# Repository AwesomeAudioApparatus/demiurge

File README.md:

# Demiurge

Demiurge is a combination of Hardware and Software for Digital Sound Processing in the Eurorack Modular Synthesizer environment.

The "Demiurge 1" board is an 8 HP Eurorack compatible board, the functionality defined in software and custom front panel can either 
be made by hand, ordered from local mechanical shops or ordered from PCB manufacturers (KiCad template for front panel exists).

The "Demiurge Sound Processing Engine" is a system to more easily create Eurorack module functionality. A simple VCO module may look like this;

```C
#include "demiurge.h"
#include "demiurge-board.h"

static control_pair_t pair1;  // frequency
static control_pair_t pair2;  // amplitude

static control_pair_t pair3;  // frequency
static control_pair_t pair4;  // amplitude

static audio_outport_t out1;
static audio_outport_t out2;
static oscillator_t oscillator1;
static oscillator_t oscillator2;

/* Simple 2 VCO. SAW on output 1 and SQUARE on output 2. */

void vco_prepare() {
    demiurge_samplerate = 48000;      // 48000 samples/second
    demiurge_set_inport_cv(1);
    demiurge_set_inport_cv(2);
    demiurge_set_inport_cv(3);
    demiurge_set_inport_cv(4);

    demiurge_set_outport_audio(1);
    demiurge_set_outport_audio(2);
}

void vco_setup() {
    // Initialize the hardware configuration
    control_pair_init(&pair1, 1);     // FREQUENCY = CV+Pot at the top
    control_pair_init(&pair2, 2);     // AMPLITUDE = CV+Pot at the second position from the top
    control_pair_init(&pair3, 3);     // FREQUENCY = CV+Pot at the third position from top
    control_pair_init(&pair4, 4);     // AMPLITUDE = CV+Pot at the bottom
    audio_outport_init(&out1, 1);     // Audio Out on left output channel
    audio_outport_init(&out2, 2);     // Audio Out on right output channel

    // Initialize the oscillators
    oscillator_init(&oscillator1);
    oscillator_init(&oscillator2);

    // Set up the oscillators to SINE wave form

    oscillator_configure_mode(&oscillator1, SAW);
    oscillator_configure_mode(&oscillator2, SQUARE);

    oscillator_configure_frequency(&oscillator1, &pair1.me);
    oscillator_configure_frequency(&oscillator2, &pair3.me);

    oscillator_configure_amplitude(&oscillator1, &pair2.me);
    oscillator_configure_amplitude(&oscillator2, &pair4.me);

    // Connect Oscillator to outputs
    audio_outport_configure_input(&out1, &oscillator1.me);
    audio_outport_configure_input(&out2, &oscillator2.me);
}

void vco_loop() {
   // handle buttons and LEDs
}

int main(void)
{
    vco_prepare();                  // Prepare the board for the functionality

    demiurge_driver_init();         // Initialize the hardware driver
    demiurge_init();                // Initialize the Demiurge platform
    vco_setup();                    // Set up the functionality
    demiurge_start();               // Start the audio processing
    while(1)
    {
        vco_loop();                 // Give time for LEDs and Buttons
    }
}

```

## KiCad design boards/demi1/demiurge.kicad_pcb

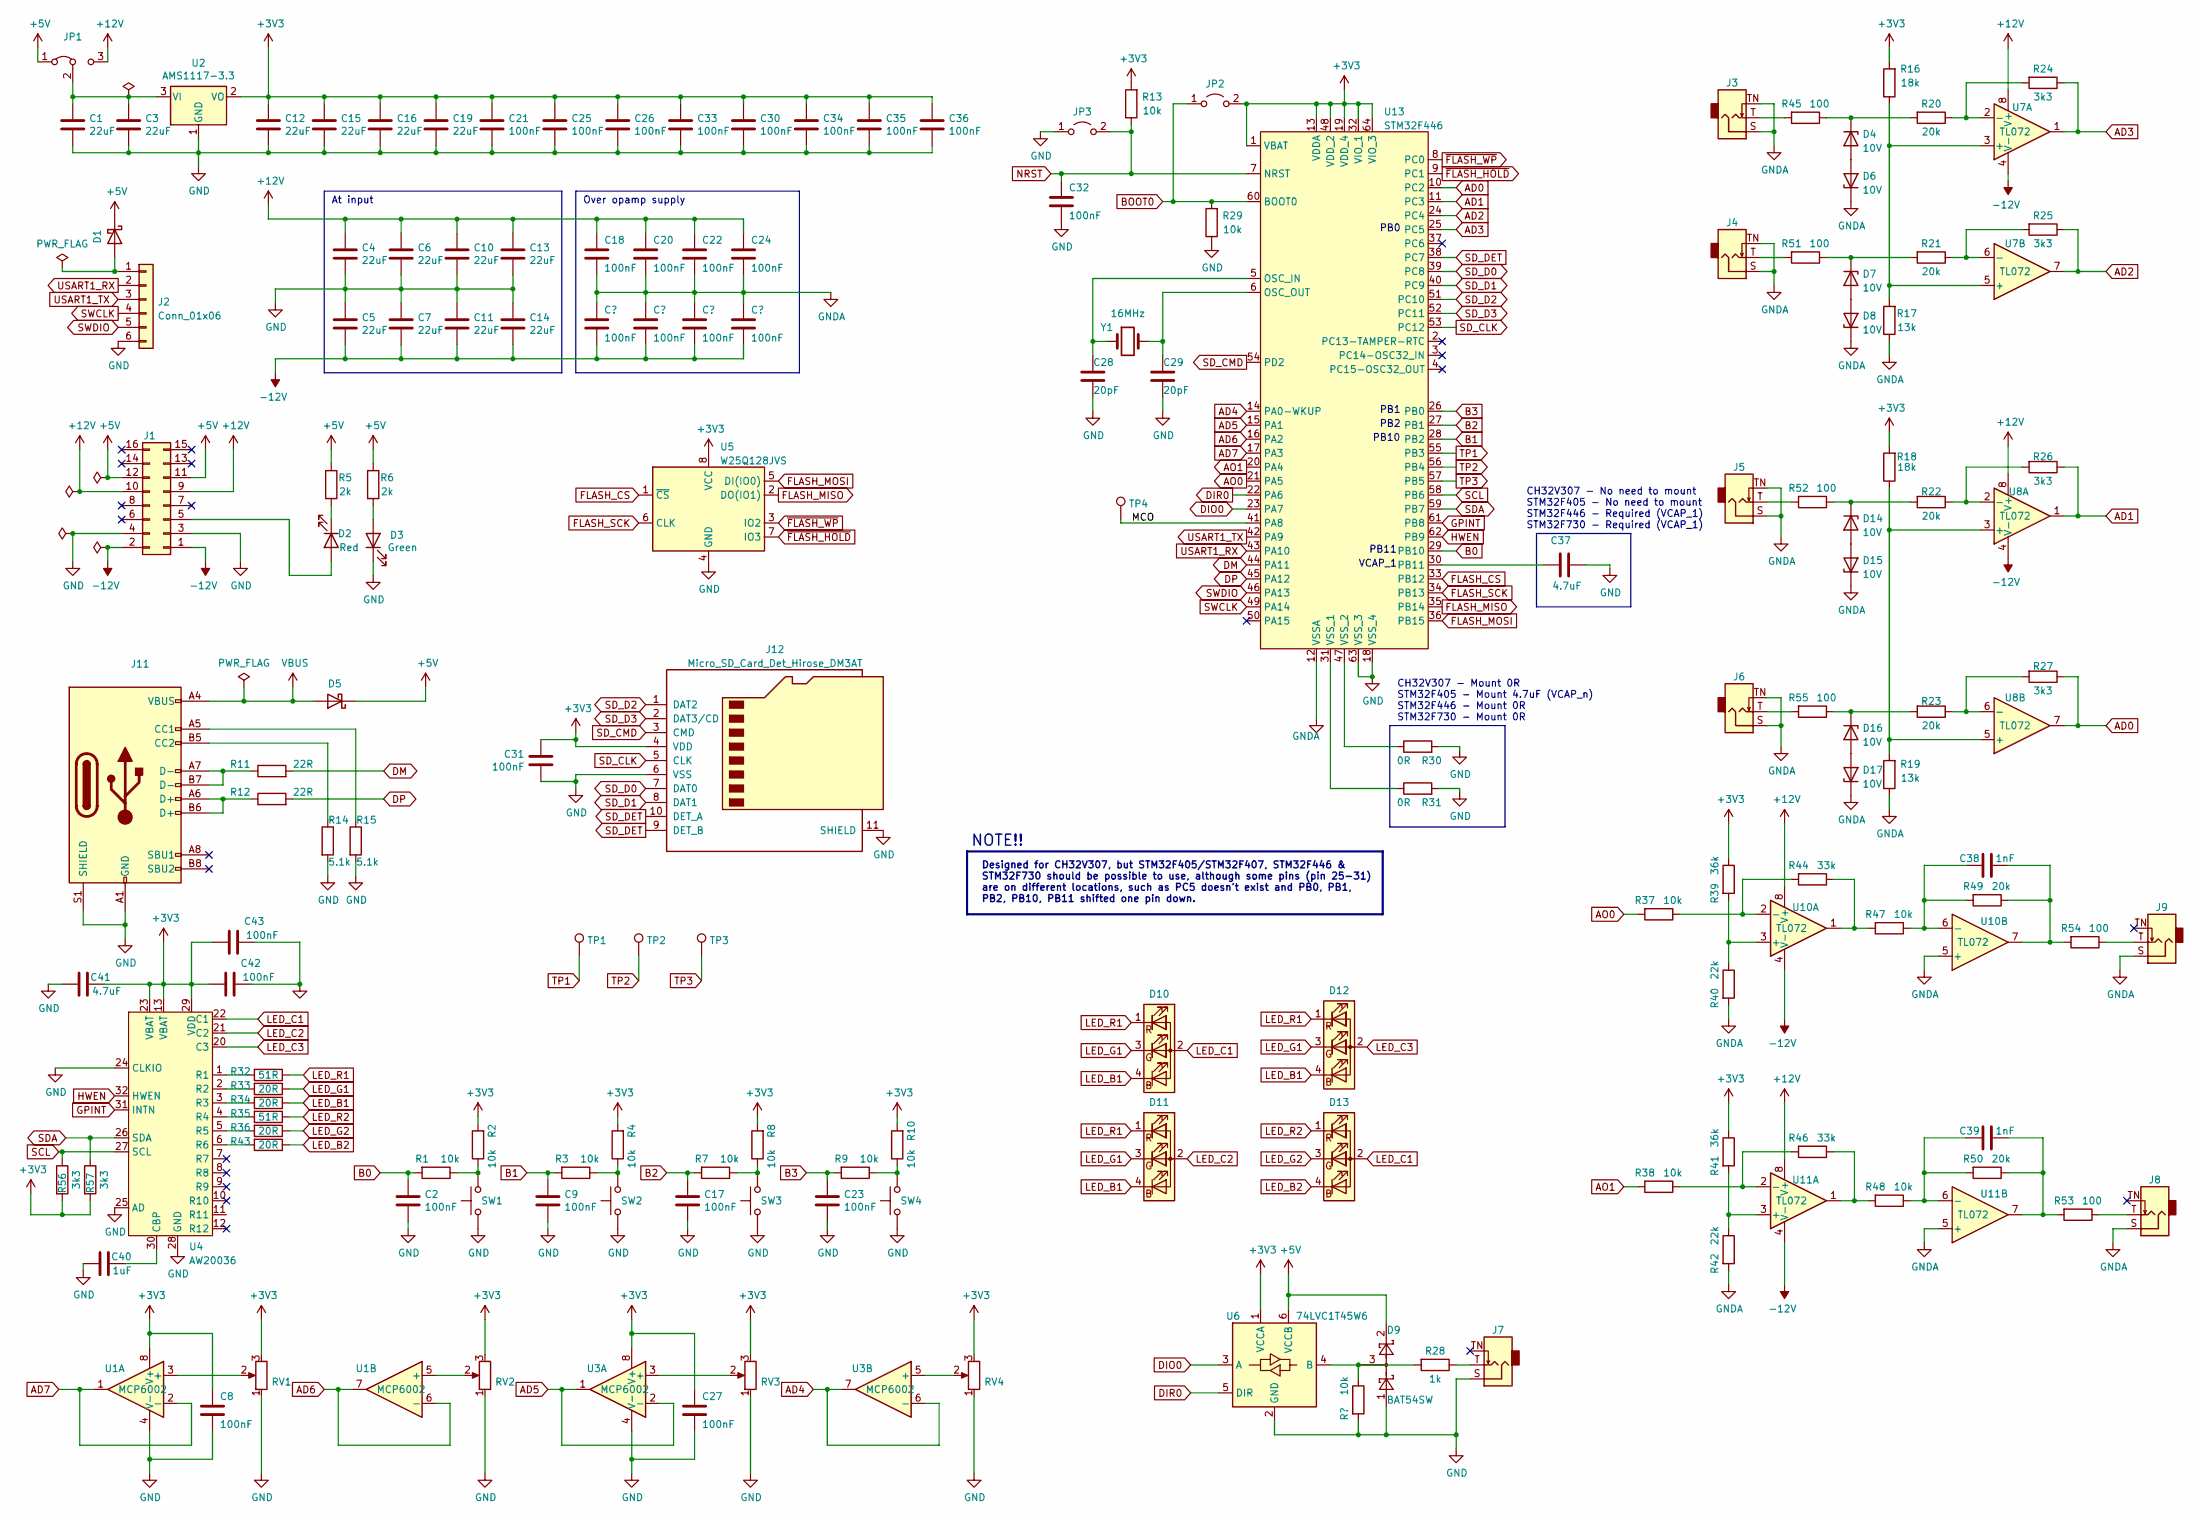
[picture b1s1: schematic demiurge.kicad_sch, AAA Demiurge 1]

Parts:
C1, C3, C4, C5, C6, C7, C10, C11, C12, C13, C14, C15, C16, C19: 22uF; C_0805_2012Metric; LCSC C129303
C2, C8, C9, C17, C18, C20, C21, C22, C23, C24, C25, C26, C27, C30, C31, C32, C33, C34, C35, C36, C42, C43: 100nF; C_0603_1608Metric; LCSC C14663
C28, C29: 20pF; C_0603_1608Metric; LCSC C1648
C37, C41: 4.7uF; C_0805_2012Metric; LCSC C19666
C38, C39: 1nF; C_0603_1608Metric; LCSC C1588
C40: 1uF; C_0603_1608Metric; LCSC C15849
D1, D5: D_SOD-123; LCSC C8598
D2: Red; LED_0603_1608Metric; LCSC C2286
D3: Green; LED_0603_1608Metric; LCSC C72043
D4, D6, D7, D8, D14, D15, D16, D17: 10V; D_SOD-323; LCSC C493185
D9: BAT54SW; SOT-323_SC-70; LCSC C78260
D10, D11, D12, D13: LED_D5.0mm-4_RGB; LCSC C331057
J1: PinHeader_2x08_P2.54mm_Vertical; LCSC C68234
J2: Conn_01x06; PinHeader_1x06_P2.54mm_Vertical; LCSC C37208
J3, J4, J5, J6, J7, J8, J9: PJ301M-12
J11: USB_C_Receptacle_Vertical; LCSC C167321
J12: Micro_SD_Card_Det_Hirose_DM3AT; microSD_HC_Hirose_DM3AT-SF-PEJM5; LCSC C114218
JP1: SolderJumper-3_P1.3mm_Bridged12_RoundedPad1.0x1.5mm
JP2, JP3: C_1206_3216Metric
R1, R2, R3, R4, R7, R8, R9, R10, R13, R29, R37, R38, R47, R48: 10k; R_0603_1608Metric; LCSC C25804
R5, R6: 2k; R_0603_1608Metric; LCSC C22975
R11, R12: 22R; R_0402_1005Metric; LCSC C25092
R14, R15: 5.1k; R_0402_1005Metric; LCSC C25905
R16, R18: 18k; R_0603_1608Metric; LCSC C25810
R17, R19: 13k; R_0603_1608Metric; LCSC C22797
R20, R21, R22, R23, R49, R50: 20k; R_0603_1608Metric; LCSC C4184
R24, R25, R26, R27, R56, R57: 3k3; R_0603_1608Metric; LCSC C22978
R28: 1k; R_0603_1608Metric; LCSC C21190
R30, R31: 0R; C_0603_1608Metric; LCSC C21189
R32, R35: 51R; R_0603_1608Metric; LCSC C23197
R33, R34, R36, R43: 20R; R_0603_1608Metric; LCSC C22950
R39, R41: 36k; R_0603_1608Metric; LCSC C23147
R40, R42: 22k; R_0603_1608Metric; LCSC C31850
R44, R46: 33k; R_0603_1608Metric; LCSC C4216
R45, R51, R52, R53, R54, R55: 100; R_0603_1608Metric; LCSC C22775
RV1, RV2, RV3, RV4: Potentiometer_Alpha_RD901F-40-00D_Single_Vertical
SW1, SW2, SW3, SW4: SW_PUSH_6mm_H8mm
TP1: TP1; TestPoint_Pad_1.5x1.5mm
TP2: TP2; TestPoint_Pad_1.5x1.5mm
TP3, TP4: SWO; TestPoint_Pad_1.5x1.5mm
U1, U3: MCP6002; SOIC-8_3.9x4.9mm_P1.27mm; LCSC C7377
U2: AMS1117-3.3; SOT-223-3_TabPin2; LCSC C6186
U4: AW20036; QFN-32-1EP_4x4mm_P0.4mm_EP2.65x2.65mm_ThermalVias; LCSC C401019
U5: W25Q128JVS; SOIC-8_5.23x5.23mm_P1.27mm; LCSC C97521
U6: 74LVC1T45W6; SOT-23-6; LCSC C7843
U7, U8, U10, U11: TL072; SOIC-8_3.9x4.9mm_P1.27mm; LCSC C6961
U13: STM32F446; LQFP-64_10x10mm_P0.5mm; LCSC C69336
Y1: 16MHz; Crystal_SMD_3225-4Pin_3.2x2.5mm; LCSC C13738

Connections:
+3V3: C8.1, C12.1, C15.1, C16.1, C19.1, C21.1, C25.1, C26.1, C27.1, C30.1, C31.1, C33.1, C34.1, C35.1, C36.1, C41.2, C42.1, C43.1, J12.4 (VDD), JP2.2 (B), R2.2, R4.2, R8.2, R10.2, R13.2, R16.2, R18.2, R39.1, R41.1, R56.2, R57.2, RV1.3, RV2.3, RV3.3, RV4.3, U1.8 (V+), U2.2 (VO), U3.8 (V+), U4.13 (VBAT), U4.23 (VBAT), U4.29 (VDD), U5.8 (VCC), U6.1 (VCCA), U13.1 (VBAT), U13.13 (VDDA), U13.19 (VDD_4), U13.32 (VIO_1), U13.48 (VDD_2), U13.64 (VIO_3)
+5V: D1.1 (K), D5.1 (K), D9.2, J1.11, J1.12, JP1.1 (A), R5.1, R6.1, U6.6 (VCCB)
+12V: C4.1, C6.1, C10.1, C13.1, C18.1, C20.1, C22.1, C24.1, J1.9, J1.10, JP1.3 (B), U7.8 (V+), U8.8 (V+), U10.8 (V+), U11.8 (V+)
/MCO: TP4.1, U13.41 (PA8)
AD0: R27.1, U8.7, U13.10 (PC2)
AD1: R26.1, U8.1, U13.11 (PC3)
AD2: R25.1, U7.7, U13.24 (PC4)
AD3: R24.1, U7.1, U13.25 (PC5)
AD4: U3.6 (-), U3.7, U13.14 (PA0-WKUP)
AD5: U3.1, U3.2 (-), U13.15 (PA1)
AD6: U1.6 (-), U1.7, U13.16 (PA2)
AD7: U1.1, U1.2 (-), U13.17 (PA3)
AO0: R37.2, U13.21 (PA5)
AO1: R38.2, U13.20 (PA4)
B0: C2.1, R1.2, U13.29 (PB10)
B1: C9.1, R3.2, U13.28 (PB2)
B2: C17.1, R7.2, U13.27 (PB1)
B3: C23.1, R9.2, U13.26 (PB0)
BOOT0: JP2.1 (A), R29.2, U13.60 (BOOT0)
DIO0: U6.3 (A), U13.23 (PA7)
DIR0: U6.5 (DIR), U13.22 (PA6)
DM: R11.2, U13.44 (PA11)
DP: R12.2, U13.45 (PA12)
FLASH_CS: U5.1 (~CS), U13.33 (PB12)
FLASH_MISO: U5.2 (DO(IO1)), U13.35 (PB14)
FLASH_MOSI: U5.5 (DI(IO0)), U13.36 (PB15)
FLASH_SCK: U5.6 (CLK), U13.34 (PB13)
GND: C1.2, C2.2, C3.2, C4.2, C5.1, C6.2, C7.1, C8.2, C9.2, C10.2, C11.1, C12.2, C13.2, C14.1, C15.2, C16.2, C17.2, C19.2, C21.2, C23.2, C25.2, C26.2, C27.2, C28.2, C29.2, C30.2, C31.2, C32.2, C33.2, C34.2, C35.2, C36.2, C37.2, C40.1, C41.1, C42.2, C43.2, D3.1 (K), D9.1, J1.3, J1.4, J2.6, J7.S, J11.A1 (GND), J11.A12 (GND), J11.B1 (GND), J11.B12 (GND), J11.S1 (SHIELD), J12.6 (VSS), J12.11 (SHIELD), JP3.1 (A), R14.2, R15.2, R29.1, R30.2, R31.2, RV1.1, RV2.1, RV3.1, RV4.1, SW1.1, SW2.1, SW3.1, SW4.1, U1.4 (V-), U2.1 (GND), U3.4 (V-), U4.24 (CLKIO), U4.25 (AD), U4.28 (GND), U5.4 (GND), U6.2 (GND), U13.18 (VSS_4), U13.63 (VSS_3)
GNDA: D6.1 (K), D8.1 (K), D15.1 (K), D17.1 (K), J3.S, J3.TN, J4.S, J4.TN, J5.S, J5.TN, J6.S, J6.TN, J8.S, J9.S, R17.1, R19.1, R40.2, R42.2, U10.5 (+), U11.5 (+), U13.12 (VSSA)
GPINT: U4.31 (INTN), U13.61 (PB8)
HWEN: U4.32 (HWEN), U13.62 (PB9)
LED_B1: D10.4 (BK), D11.4 (BK), D12.4 (BK), R34.1
LED_B2: D13.4 (BK), R43.1
LED_C1: D10.2 (A), D13.2 (A), U4.22 (C1)
LED_C2: D11.2 (A), U4.21 (C2)
LED_C3: D12.2 (A), U4.20 (C3)
LED_G1: D10.3 (GK), D11.3 (GK), D12.3 (GK), R33.1
LED_G2: D13.3 (GK), R36.1
LED_R1: D10.1 (RK), D11.1 (RK), D12.1 (RK), R32.1
LED_R2: D13.1 (RK), R35.1
NRST: C32.1, JP3.2 (B), R13.1, U13.7 (NRST)
unnamed: C1.1, C3.1, JP1.2 (C), U2.3 (VI)
unnamed: C28.1, U13.5 (OSC_IN), Y1.1
unnamed: C29.1, U13.6 (OSC_OUT), Y1.2
unnamed: C37.1, U13.30 (PB11)
unnamed: C38.1, R47.1, R49.2, U10.6 (-)
unnamed: C38.2, R49.1, R54.2, U10.7
unnamed: C39.1, R48.1, R50.2, U11.6 (-)
unnamed: C39.2, R50.1, R53.2, U11.7
unnamed: C40.2, U4.30 (CBP)
unnamed: D1.2 (A), J2.1
unnamed: D2.1 (K), R5.2
unnamed: D2.2 (A), J1.5
unnamed: D3.2 (A), R6.2
unnamed: D4.1 (K), R20.2, R45.1
unnamed: D4.2 (A), D6.2 (A)
unnamed: D7.1 (K), R21.2, R51.1
unnamed: D7.2 (A), D8.2 (A)
unnamed: D9.3, R28.2, U6.4 (B)
unnamed: D14.1 (K), R22.2, R52.1
unnamed: D14.2 (A), D15.2 (A)
unnamed: D16.1 (K), R23.2, R55.1
unnamed: D16.2 (A), D17.2 (A)
unnamed: J3.T, R45.2
unnamed: J4.T, R51.2
unnamed: J5.T, R52.2
unnamed: J6.T, R55.2
unnamed: J7.T, R28.1
unnamed: J8.T, R53.1
unnamed: J9.T, R54.1
unnamed: J11.A5 (CC1), R15.1
unnamed: J11.A6 (D+), J11.B6 (D+), R12.1
unnamed: J11.A7 (D-), J11.B7 (D-), R11.1
unnamed: J11.B5 (CC2), R14.1
unnamed: R1.1, R2.1, SW1.2
unnamed: R3.1, R4.1, SW2.2
unnamed: R7.1, R8.1, SW3.2
unnamed: R9.1, R10.1, SW4.2
unnamed: R16.1, R17.2, U7.3 (+), U7.5 (+)
unnamed: R18.1, R19.2, U8.3 (+), U8.5 (+)
unnamed: R20.1, R24.2, U7.2 (-)
unnamed: R21.1, R25.2, U7.6 (-)
unnamed: R22.1, R26.2, U8.2 (-)
unnamed: R23.1, R27.2, U8.6 (-)
unnamed: R30.1, U13.47 (VSS_2)
unnamed: R31.1, U13.31 (VSS_1)
unnamed: R32.2, U4.1 (R1)
unnamed: R33.2, U4.2 (R2)
unnamed: R34.2, U4.3 (R3)
unnamed: R35.2, U4.4 (R4)
unnamed: R36.2, U4.5 (R5)
unnamed: R37.1, R44.2, U10.2 (-)
unnamed: R38.1, R46.2, U11.2 (-)
unnamed: R39.2, R40.1, U10.3 (+)
unnamed: R41.2, R42.1, U11.3 (+)
unnamed: R43.2, U4.6 (R6)
unnamed: R44.1, R47.2, U10.1
unnamed: R46.1, R48.2, U11.1
unnamed: RV1.2, U1.3 (+)
unnamed: RV2.2, U1.5 (+)
unnamed: RV3.2, U3.3 (+)
unnamed: RV4.2, U3.5 (+)
SCL: R56.1, U4.27 (SCL), U13.58 (PB6)
SDA: R57.1, U4.26 (SDA), U13.59 (PB7)
SD_CLK: J12.5 (CLK), U13.53 (PC12)
SD_CMD: J12.3 (CMD), U13.54 (PD2)
SD_D0: J12.7 (DAT0), U13.39 (PC8)
SD_D1: J12.8 (DAT1), U13.40 (PC9)
SD_D2: J12.1 (DAT2), U13.51 (PC10)
SD_D3: J12.2 (DAT3/CD), U13.52 (PC11)
SD_DET: J12.9 (DET_B), J12.10 (DET_A), U13.38 (PC7)
SWCLK: J2.4, U13.49 (PA14)
SWDIO: J2.5, U13.46 (PA13)
TP1: TP1.1, U13.55 (PB3)
TP2: TP2.1, U13.56 (PB4)
TP3: TP3.1, U13.57 (PB5)
USART1_RX: J2.2, U13.43 (PA10)
USART1_TX: J2.3, U13.42 (PA9)
VBUS: D5.2 (A), J11.A4 (VBUS), J11.A9 (VBUS), J11.B4 (VBUS), J11.B9 (VBUS)
~FLASH_HOLD: U5.7 (IO3), U13.9 (PC1)
~FLASH_WP: U5.3 (IO2), U13.8 (PC0)

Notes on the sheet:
Designed for CH32V307, but STM32F405/STM32F407, STM32F446 & STM32F730 should be possible to use, although some pins (pin 25-31) are on different locations, such as PC5 doesn't exist and PB0, PB1, PB2, PB10, PB11 shifted one pin down.
At input
PB0
VCAP_1
PB10
NOTE!!
PB11
CH32V307 - No need to mount STM32F405 - No need to mount STM32F446 - Required (VCAP_1) STM32F730 - Required (VCAP_1)
CH32V307 - Mount 0R STM32F405 - Mount 4.7uF (VCAP_n) STM32F446 - Mount 0R STM32F730 - Mount 0R
PB1
Over opamp supply
PB2

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
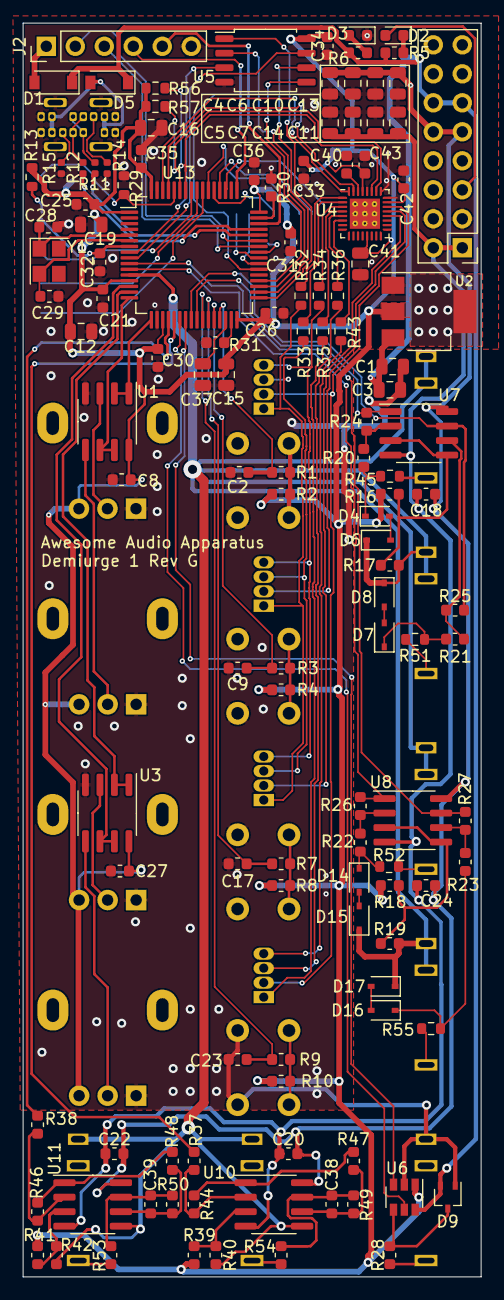
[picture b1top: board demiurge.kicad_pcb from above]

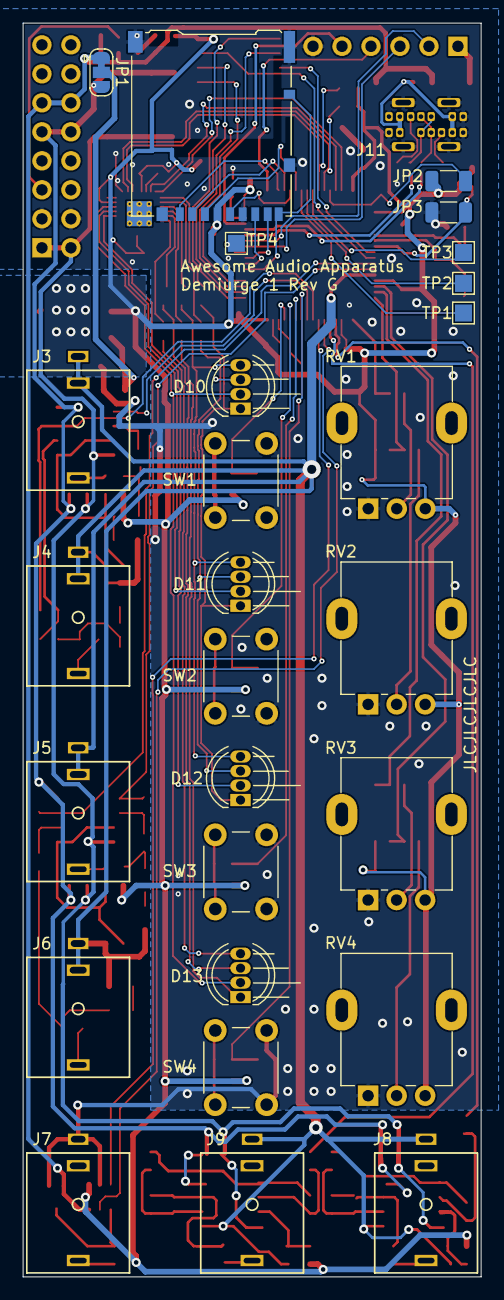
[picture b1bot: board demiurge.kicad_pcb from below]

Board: 2 copper layers, 40.1 x 109.9 mm, 155 parts (28 on the bottom side), 122 nets.

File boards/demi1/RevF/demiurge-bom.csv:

Comment,Designator,Footprint,LCSC
"22uF","C1,C3,C4,C5,C6,C7,C10,C11,C12,C13,C14,C15,C16,C19","Capacitor_SMD:C_0805_2012Metric","C129303"
"100nF","C2,C8,C9,C17,C18,C20,C21,C22,C23,C24,C25,C26,C27,C30,C31,C32,C33,C34,C35,C36,C42,C43","Capacitor_SMD:C_0603_1608Metric","C14663"
"20pF","C28,C29","Capacitor_SMD:C_0603_1608Metric","C1648"
"4.7uF","C37,C41","Capacitor_SMD:C_0805_2012Metric","C19666"
"1nF","C38,C39","Capacitor_SMD:C_0603_1608Metric","C1588"
"1uF","C40","Capacitor_SMD:C_0603_1608Metric","C15849"
"~","D1,D5","Diode_SMD:D_SOD-123","C8598"
"~","D10,D11,D12,D13","LED_THT:LED_D5.0mm-4_RGB","C331057"
"Red","D2","LED_SMD:LED_0603_1608Metric","C2286"
"Green","D3","LED_SMD:LED_0603_1608Metric","C72043"
"10V","D4,D6,D7,D8,D14,D15,D16,D17","Diode_SMD:D_SOD-323","C493185"
"BAT54SW","D9","Package_TO_SOT_SMD:SOT-323_SC-70","C78260"
"~","J1","Connector_PinHeader_2.54mm:PinHeader_2x08_P2.54mm_Vertical","C68234"
"~","J11","aaa:USB_C_Receptacle_Vertical","C167321"
"Micro_SD_Card_Det_Hirose_DM3AT","J12","Connector_Card:microSD_HC_Hirose_DM3AT-SF-PEJM5","C114218"
"Conn_01x06","J2","Connector_PinHeader_2.54mm:PinHeader_1x06_P2.54mm_Vertical","C37208"
"~","J3,J4,J5,J6,J7,J8,J9","aaa:PJ301M-12"
"~","JP1","Jumper:SolderJumper-3_P1.3mm_Bridged12_RoundedPad1.0x1.5mm"
"~","JP2,JP3","Capacitor_SMD:C_1206_3216Metric"
"10k","R1,R2,R3,R4,R7,R8,R9,R10,R13,R29,R37,R38,R47,R48","Resistor_SMD:R_0603_1608Metric","C25804"
"22R","R11,R12","Resistor_SMD:R_0402_1005Metric","C25092"
"5.1k","R14,R15","Resistor_SMD:R_0402_1005Metric","C25905"
"18k","R16,R18","Resistor_SMD:R_0603_1608Metric","C25810"
"13k","R17,R19","Resistor_SMD:R_0603_1608Metric","C22797"
"20k","R20,R21,R22,R23,R49,R50","Resistor_SMD:R_0603_1608Metric","C4184"
"3k3","R24,R25,R26,R27","Resistor_SMD:R_0603_1608Metric","C22978"
"1k","R28","Resistor_SMD:R_0603_1608Metric","C21190"
"0R","R30,R31","Capacitor_SMD:C_0603_1608Metric","C21189"
"51R","R32,R35","Resistor_SMD:R_0603_1608Metric","C23197"
"20R","R33,R34,R36,R43","Resistor_SMD:R_0603_1608Metric","C22950"
"36k","R39,R41","Resistor_SMD:R_0603_1608Metric","C23147"
"22k","R40,R42","Resistor_SMD:R_0603_1608Metric","C31850"
"33k","R44,R46","Resistor_SMD:R_0603_1608Metric","C4216"
"100","R45,R51,R52,R53,R54,R55","Resistor_SMD:R_0603_1608Metric","C22775"
"2k","R5,R6","Resistor_SMD:R_0603_1608Metric","C22975"
"~","RV1,RV2,RV3,RV4","aaa:Potentiometer_Alpha_RD901F-40-00D_Single_Vertical"
"~","SW1,SW2,SW3,SW4","Button_Switch_THT:SW_PUSH_6mm_H8mm"
"TP1","TP1","TestPoint:TestPoint_Pad_1.5x1.5mm"
"TP2","TP2","TestPoint:TestPoint_Pad_1.5x1.5mm"
"SWO","TP3,TP4","TestPoint:TestPoint_Pad_1.5x1.5mm"
"MCP6002","U1,U3","Package_SO:SOIC-8_3.9x4.9mm_P1.27mm","C7377"
"CH32V307RCT6","U13","Package_QFP:LQFP-64_10x10mm_P0.5mm","CH32V307RCT6"
"AMS1117-3.3","U2","Package_TO_SOT_SMD:SOT-223-3_TabPin2","C6186"
"AW20036","U4","Package_DFN_QFN:QFN-32-1EP_4x4mm_P0.4mm_EP2.65x2.65mm_ThermalVias","C401019"
"W25Q128JVS","U5","Package_SO:SOIC-8_5.23x5.23mm_P1.27mm","C97521"
"74LVC1T45W6","U6","Package_TO_SOT_SMD:SOT-23-6","C7843"
"TL072","U7,U8,U10,U11","Package_SO:SOIC-8_3.9x4.9mm_P1.27mm","C6961"
"16MHz","Y1","Crystal:Crystal_SMD_3225-4Pin_3.2x2.5mm","C13738"

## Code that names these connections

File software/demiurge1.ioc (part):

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Mcu.Name=STM32F446R(C-E)Tx
Mcu.Package=LQFP64
Mcu.UserName=STM32F446RETx
PA0-WKUP.Signal=ADCx_IN0
PA1.Signal=ADCx_IN1
PA10.Mode=Asynchronous
PA10.Signal=USART1_RX
PA11.Signal=USB_OTG_FS_DM
PA12.Signal=USB_OTG_FS_DP
PA13.Mode=Serial_Wire
PA13.Signal=SYS_JTMS-SWDIO
PA14.Mode=Serial_Wire
PA14.Signal=SYS_JTCK-SWCLK
PA2.Signal=ADCx_IN2
PA3.Signal=ADCx_IN3
PA4.Signal=COMP_DAC1_group
PA5.Signal=COMP_DAC2_group
PA6.Signal=GPIO_Output
PA7.Signal=GPIO_Input
PA8.Mode=Clock-out-1
PA8.Signal=RCC_MCO_1
PA9.Mode=Asynchronous
PA9.Signal=USART1_TX
PB0.Signal=GPIO_Input
PB1.Signal=GPIO_Input
PB10.Signal=GPIO_Input
PB12.Mode=NSS_Signal_Hard_Output
PB12.Signal=SPI2_NSS
PB13.Mode=Full_Duplex_Master
PB13.Signal=SPI2_SCK
PB14.Mode=Full_Duplex_Master
PB14.Signal=SPI2_MISO
PB15.Mode=Full_Duplex_Master
PB15.Signal=SPI2_MOSI
PB2.Signal=GPIO_Input
PB3.Signal=GPIO_Output
PB4.Signal=GPIO_Output
PB5.Signal=GPIO_Output
PB6.Mode=I2C
PB6.Signal=I2C1_SCL
PB7.Mode=I2C
PB7.Signal=I2C1_SDA
PB8.Signal=GPIO_Input
PB9.GPIOParameters=PinState
PB9.PinState=GPIO_PIN_RESET
PB9.Signal=GPIO_Output
PC0.Signal=GPIO_Output
PC1.Signal=GPIO_Output
PC10.Signal=SDIO_D2
PC11.Signal=SDIO_D3
PC12.Signal=SDIO_CK
PC2.Signal=ADCx_IN12
PC3.Signal=ADCx_IN13
PC4.Signal=ADCx_IN14
PC5.Signal=ADCx_IN15
PC7.Signal=GPIO_Input
PC8.Signal=SDIO_D0
PC9.Signal=SDIO_D1
PD2.Signal=SDIO_CMD
PH0-OSC_IN.Mode=HSE-External-Oscillator
PH0-OSC_IN.Signal=RCC_OSC_IN
PH1-OSC_OUT.Mode=HSE-External-Oscillator
PH1-OSC_OUT.Signal=RCC_OSC_OUT
RCC.HSE_Timout=200
RCC.HSE_VALUE=16000000
RCC.SYSCLKFreq_VALUE=180000000
RCC.SYSCLKSource=RCC_SYSCLKSOURCE_PLLCLK
board=custom

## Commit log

2022-05-20 Adding HW design.
2022-05-20 Added USB1/USB2 labels. What should we do with 2 USB ports?
2022-06-25 First cut of the software. Not changed to RISC-V yet.
2022-06-26 First running on the generic devkit.
2022-07-02 Restructuring in attempt to support multiple hardwares.
2022-07-04 DAC should be working as expected now.
2022-07-04 fixing tab->spaces
2022-07-05 troubleshooting
2022-07-05 adc working
2022-07-09 Fixed driver for ADC conversion. Worked on octave_per_volt
2022-07-10 Fixing NVIC priorities, to stablize frequency.
2022-07-10 Change the license.
2022-07-12 Trying to get Flash working, but there are something causing time-dependency and the function is not working yet.
2022-08-04 Rev E updated to Rev F (WIP)
2022-08-04 AW9523 is discontinued @ LCSC. Changing to AW20036, capable of up to 12 RGB LEDs.
2022-08-05 Massive restructuring to start supporting additional boards and MCUs.
2022-08-06 Rearrange the hardware part as well, to allow more boards, and put submodule link to libraries.
2022-08-06 formatting
2022-08-06 Defined 3 build targets. 'startup' seems to be a reserved word in MOunRiver or something, so renaming the startup folder with the initial assembler.
2022-08-06 Finalizing reshuffle of hardware.
2022-08-06 New libs version
2022-08-06 New libs
2022-08-09 Adding testpad for MCO pin, for instance to check clock speeds.
2022-08-09 Fixed adsr, and the speed is back to 144MHz.
2022-08-10 Various fixes and got to the VCO+Envelope+VCA demo.
2022-08-11 Slow down the Flash access, made it more reliable. Also set both APB busses to 144MHz
2022-08-11 RevF order made at jlcpcb.
2022-08-11 Adding README
2022-08-11 Adding front panel template
2022-08-11 Spelling fixed.
2022-08-11 Filled background in drawings.
2022-08-11 Updating docs.
2022-08-11 Updating block diagram.
2022-08-12 Detailing the frontpanel template.
2022-08-12 Front panel template submitted for manufacturing.
2022-08-14 Added schematics plot
2022-08-14 Artwork and photo
2022-08-14 Another sized logo
2022-08-16 Artwork and photos
2022-08-16 Nail down the octave/volt function
2022-08-16 A little bit docs for the oscillator function block.
2022-08-16 Removed inverted output on the sample Envelope. Not sure if the 'output buffer' is disabled by default or not. Make it explicit.
2022-08-22 Work on the build system and not be dependent on MounRiver.
2022-08-22 More build system tweaks.
2022-08-22 Update documentation
2022-09-03 Forgot I2C resistors. Grrr...
2022-09-03 Adding comment that STM32F446 can also be used.
2022-09-03 adding photos of the board
2022-10-05 LEDs working
2022-10-05 RevG using STM32F446.
2022-11-02 Halfway point to get STM32 dev environment and STM32CubeMX Pack publishing working.
2022-11-03 Getting close to a working dev environment.
2022-11-03 Tuning the build/IDE system for development. Added TIM3 interrupt handler in .ioc file.
2022-11-04 ADC and DAC working.
2022-11-05 PB9 was not an Output
2022-11-08 Buttons and LEDs are now working.
2022-11-09 STM pack
2022-11-09 Photos added.
2022-11-09 Missing functions in header files.
2022-11-09 Pack files
2022-11-10 Copy/paste error.
2022-11-10 Offset by 1 mistake.
2022-11-12 Get the ADC channels in the right spots.
2022-11-12 0.4.4 pack
2023-02-19 wrong file names on RevG photos.
